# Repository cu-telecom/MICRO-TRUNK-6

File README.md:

# Micro Trunk 6

This adapter breaks out the telephone lines on an RJ21 connector into 6 "trunk" ports made up of 4 lines, presented as 8p8c (RJ45) connectors using the [T568A wiring scheme](https://docs.cutel.net/technical/wiring/).

It's primarily designed for use with the Cisco VG224 Voice Gateways and has been designed in such a way that it won't foul devices above or below the gateway when racked, but may work with other devices.

It was created for a couple reasons:

1) Smaller, less dense deployments might not want all 24 lines broken out in one location. This adapter lets you use standard 4 pair "CAT5" cable to distribute telephone lines over longer distances, and potentially daisy chain subscriber break outs.
2) It removes the need for an RJ21 cable. These can be expensive and hard to come by, or just too bulky and unwieldy when you want to lab something.

To keep costs down, the connectors are sourced from AliExpress. You may find you can procure connectors with the same footprint from other more reputable vendors.

# Revisions

## v0.1

### Construction

You'll need:

- 2x 2mm M3 Nylon Spacer
- 2x 4mm M3 Nylon Spacer
- 2x Bolts:
	- 13-15mm M3 or 4-40 UNC bolts for friction fit mounting
	- 3/4" 4-40 UNC bolts for screw mounting
- 2x Nuts
- 6x Vertical 8p8c - https://www.aliexpress.com/item/32918645271.html
- 1x 50 pin Male RJ21 - https://www.aliexpress.com/item/1005006204411796.html
 
### Quirks

The first revision has a few "quirks" that might be positives or negatives depending on your application.

 #### The 8p8c connector pins are exposed on the back
 
 Whilst the VG224 will be protected against short circuits and other transients, a curious or misplaced finger might come into contact with "Ring Voltage" which is known to give a painful but usually non-lethal shock. This probably isn't appropriate for situations where "the public" might have access to the adapter.

On the plus side, the lack of rear insulator plate simplifies construction and lowers the cost, and will probably be fine for lab use.

#### Screwing the adapter into the VG224 can be challenging

Due to the layout of the insulator board, spacers, and connector, it can be difficult to line everything up to screw the adapter into the mounts on the VG224.

If you have a strong desire to screw it into the mounts, I'd suggest doing it once, ideally with the VG224 removed from the rack, and leaving it on there.

Alternatively, the adapter will remain in place with friction perfectly well if its not going to have the cables yanked.

#### Size

The above "quirks" mean the board is relatively compact. Fixing the quirks will require a larger board, although it'll still fit in the 1U footprint. 

## v0.2

The v0.2 attempts to address some of the above quirks by adding a rear insulator and modifying the spacers and mounting to make it easier to screw into the VG224 connector.

It's still in the design phase.

# License 

This project is licensed under the MIT license

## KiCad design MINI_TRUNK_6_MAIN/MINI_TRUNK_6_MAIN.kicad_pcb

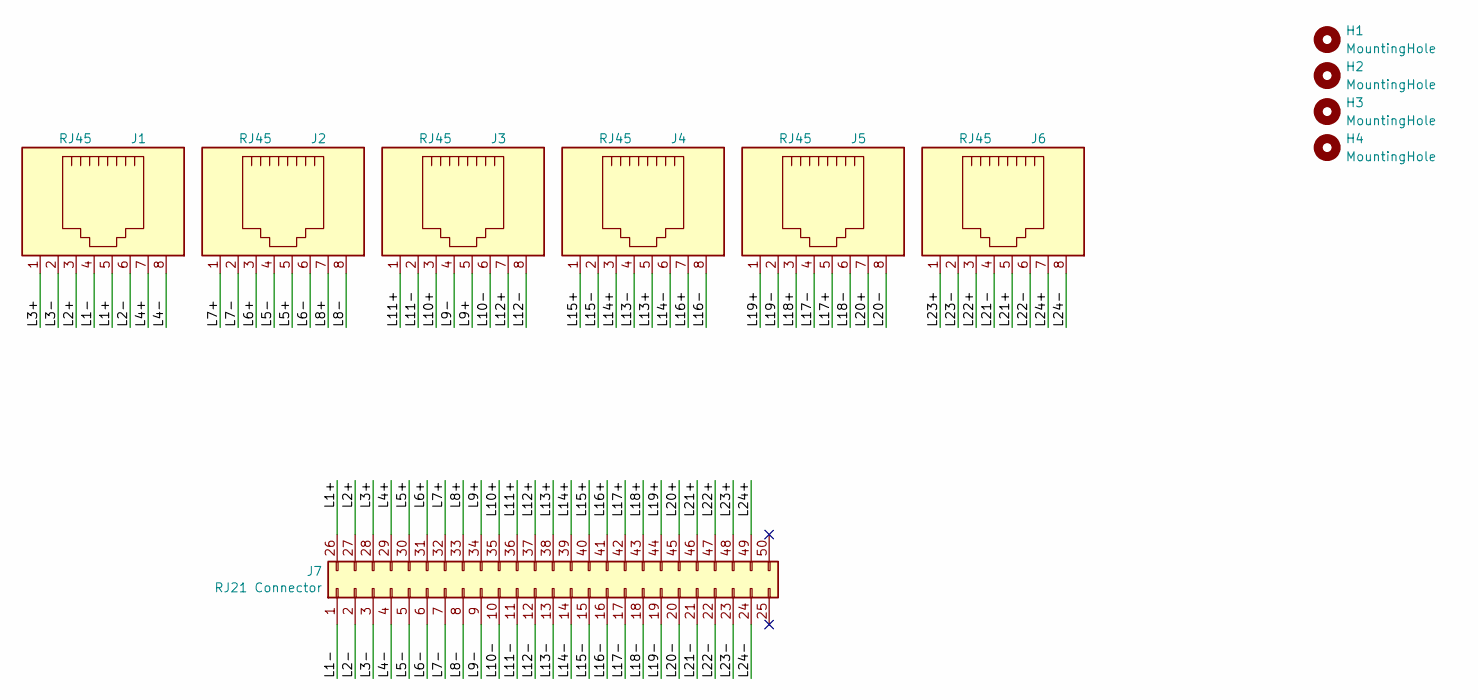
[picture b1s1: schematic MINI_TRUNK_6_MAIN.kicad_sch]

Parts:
H1, H2, H3, H4: MountingHole; MountingHole_3.2mm_M3
J1, J2, J3, J4, J5, J6: RJ45
J7: RJ21 Connector; RJ21

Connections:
/L1+: J1.5, J7.26
/L1-: J1.4, J7.1
/L2+: J1.3, J7.27
/L2-: J1.6, J7.2
/L3+: J1.1, J7.28
/L3-: J1.2, J7.3
/L4+: J1.7, J7.29
/L4-: J1.8, J7.4
/L5+: J2.5, J7.30
/L5-: J2.4, J7.5
/L6+: J2.3, J7.31
/L6-: J2.6, J7.6
/L7+: J2.1, J7.32
/L7-: J2.2, J7.7
/L8+: J2.7, J7.33
/L8-: J2.8, J7.8
/L9+: J3.5, J7.34
/L9-: J3.4, J7.9
/L10+: J3.3, J7.35
/L10-: J3.6, J7.10
/L11+: J3.1, J7.36
/L11-: J3.2, J7.11
/L12+: J3.7, J7.37
/L12-: J3.8, J7.12
/L13+: J4.5, J7.38
/L13-: J4.4, J7.13
/L14+: J4.3, J7.39
/L14-: J4.6, J7.14
/L15+: J4.1, J7.40
/L15-: J4.2, J7.15
/L16+: J4.7, J7.41
/L16-: J4.8, J7.16
/L17+: J5.5, J7.42
/L17-: J5.4, J7.17
/L18+: J5.3, J7.43
/L18-: J5.6, J7.18
/L19+: J5.1, J7.44
/L19-: J5.2, J7.19
/L20+: J5.7, J7.45
/L20-: J5.8, J7.20
/L21+: J6.5, J7.46
/L21-: J6.4, J7.21
/L22+: J6.3, J7.47
/L22-: J6.6, J7.22
/L23+: J6.1, J7.48
/L23-: J6.2, J7.23
/L24+: J6.7, J7.49
/L24-: J6.8, J7.24

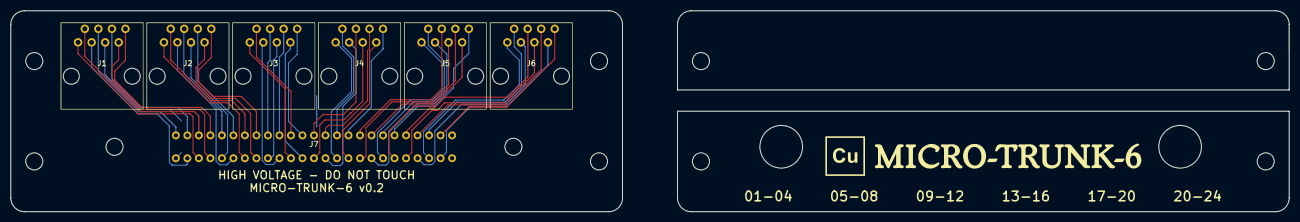
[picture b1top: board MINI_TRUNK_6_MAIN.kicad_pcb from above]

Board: 2 copper layers, 114.8 x 37.7 mm, 15 parts (0 on the bottom side), 48 nets.

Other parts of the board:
H1#2, H1#3, H3#2, H3#3: MountingHole; MountingHole_3.2mm_M3

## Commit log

2024-06-26 init
2024-07-19 Add .gitignore
2024-07-19 nearing completion
2024-07-20 Latest changes
2024-07-20 Latest updates
2024-07-20 Migrate insulators to seperate projects
2024-08-12 prep for v0.2 fabrication
2024-08-12 Final changes before fabrication
2024-08-20 Add README and LICENSE
